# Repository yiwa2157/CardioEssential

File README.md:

# CardioEssential
This repo has the code for controlling the MCU on CardioWear. MCU listens to different commands through UART, and start sampling different signals.
command = "A" : sampling and transmitting ECG signal @ 200Hz
command = "B" : sampling and transmitting temperature signal 
command = "C" : stop sampling, enter idle mode

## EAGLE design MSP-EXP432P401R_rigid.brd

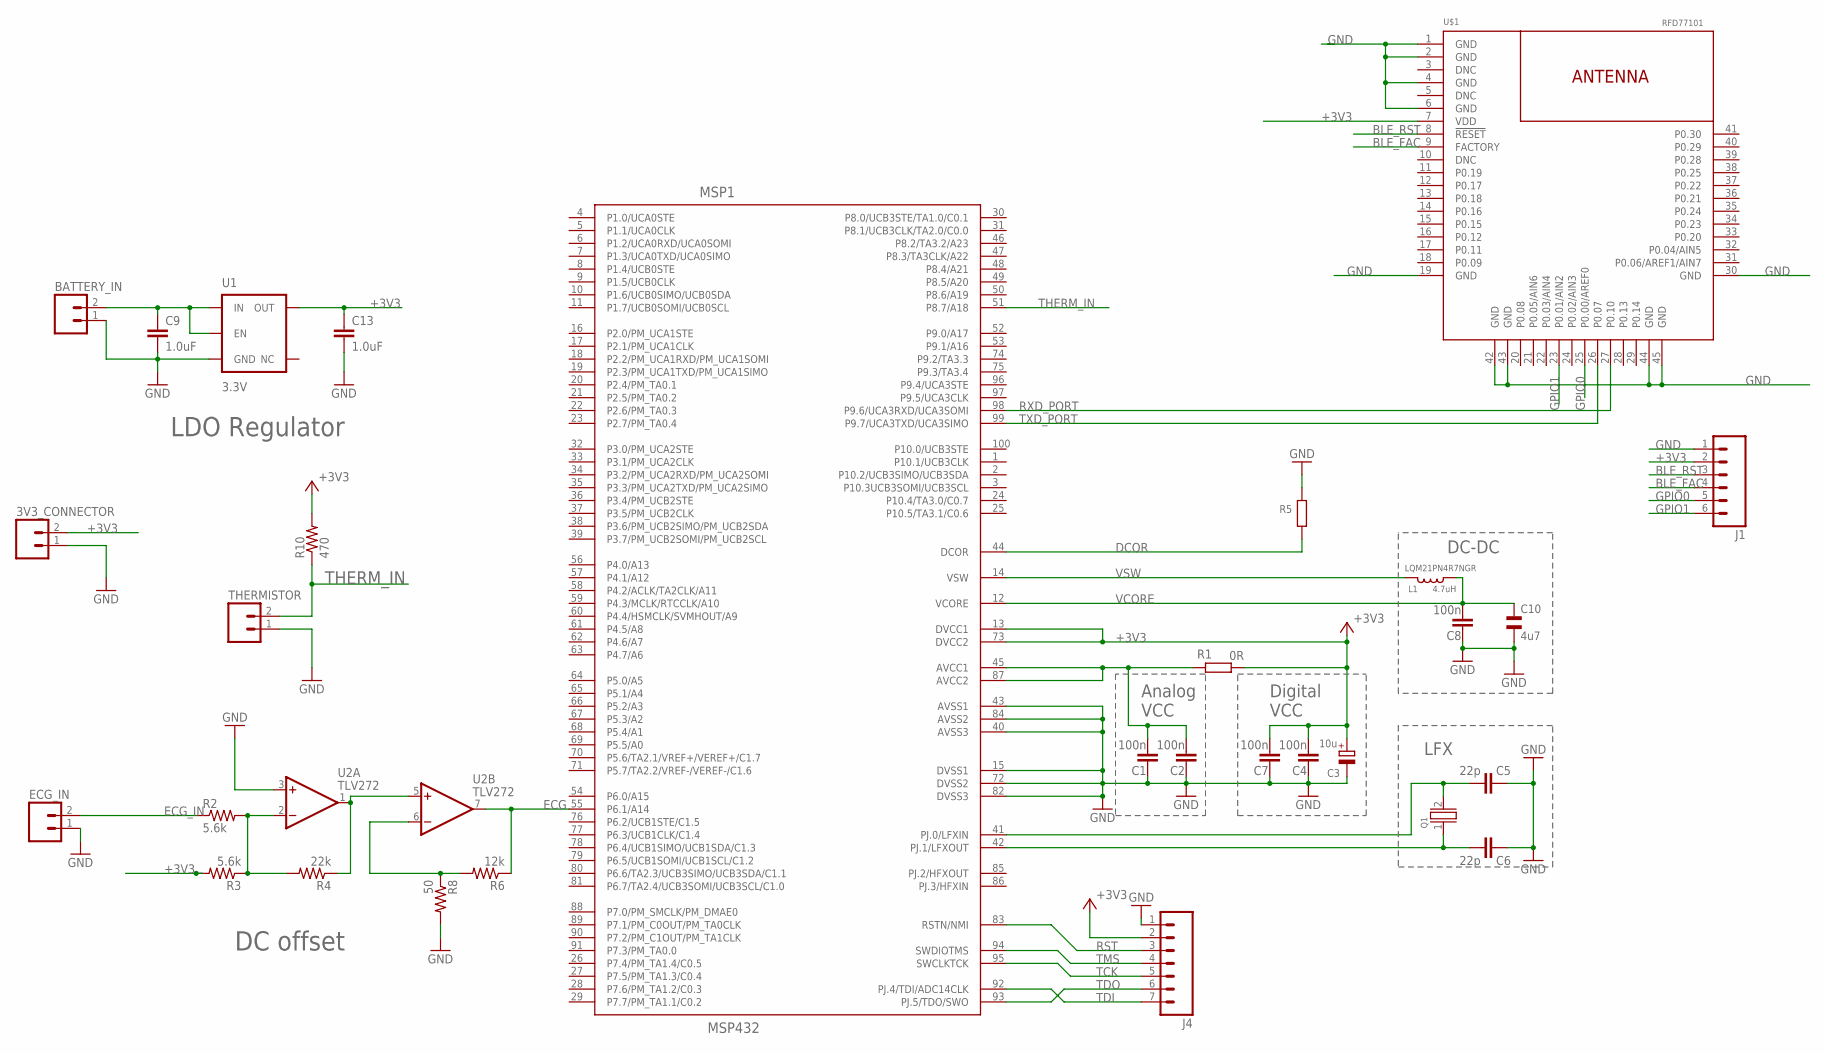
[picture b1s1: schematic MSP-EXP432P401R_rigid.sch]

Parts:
3V3_CONNECTOR: M02PTH; 1X02
BATTERY_IN: M02PTH; 1X02
C1, C2, C4, C7, C8: 100n; 0402
C3: 10u; A/3216-18R
C5, C6: 22p; 0402
C9, C13: 1.0uF; 0805-CAP
C10: 4u7; CSMD0805
ECG_IN: M02PTH; 1X02
J1: M06SILK_FEMALE_PTH; 1X06
J4: M07; 1X07
L1: 4.7uH; 0806
MSP1: MSP432; PZ100
Q1: CRYSTALLF_GENERAL; LF_XTAL
R1: 0R; 0402
R2, R3: 5.6k; 0402-RES
R4: 22k; 0402-RES
R5: R_0805; 0805
R6: 12k; 0402-RES
R8: 50; 0402-RES
R10: 470; 0402-RES
THERMISTOR: M02PTH; 1X02
U1: 3.3V; SOT23-5
U2: TLV272; SO08
U$1: RFD77101

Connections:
+3V3: 3V3_CONNECTOR.2, C3.+, C4.1, C7.1, C13.1, J1.2, J4.2, MSP1.13 (DVCC1), MSP1.73 (DVCC2), R1.1, R3.2, R10.2, U1.5 (OUT), U$1.7 (VDD)
BLE_FAC: J1.4, U$1.9 (FACTORY)
BLE_RST: J1.3, U$1.8 (!RESET!)
DCOR: MSP1.44 (DCOR), R5.1
ECG: MSP1.55 (P6.1/A14), R6.1, U2.7 (OUT)
ECG_IN: ECG_IN.2, R2.1
GND: 3V3_CONNECTOR.1, BATTERY_IN.1, C1.2, C2.2, C3.-, C4.2, C5.2, C6.2, C7.2, C8.2, C9.2, C10.2, C13.2, ECG_IN.1, J1.1, J4.1, MSP1.15 (DVSS1), MSP1.40 (AVSS3), MSP1.43 (AVSS1), MSP1.72 (DVSS2), MSP1.82 (DVSS3), MSP1.84 (AVSS2), R5.2, R8.2, THERMISTOR.1, U1.2 (GND), U2.3 (+IN), U$1.1 (GND), U$1.2 (GND), U$1.4 (GND), U$1.6 (GND), U$1.19 (GND), U$1.30 (GND), U$1.42 (GND), U$1.43 (GND), U$1.44 (GND), U$1.45 (GND)
GPIO0: J1.5, U$1.25 (P0.00/AREF0)
GPIO1: J1.6, U$1.23 (P0.01/AIN2)
unnamed: BATTERY_IN.2, C9.1, U1.1 (IN), U1.3 (EN)
unnamed: R2.2, R3.1, R4.2, U2.2 (-IN)
unnamed: C1.1, C2.1, MSP1.45 (AVCC1), MSP1.87 (AVCC2), R1.2
unnamed: R4.1, U2.1 (OUT), U2.5 (+IN)
unnamed: R6.2, R8.1, U2.6 (-IN)
unnamed: C6.1, MSP1.42 (PJ.1/LFXOUT), Q1.1
unnamed: C5.1, MSP1.41 (PJ.0/LFXIN), Q1.2
P1.0/UCA0STE: MSP1.4 (P1.0/UCA0STE)
P1.1/UCA0CLK: MSP1.5 (P1.1/UCA0CLK)
P1.2/UCA0RXD/UCA0SOMI: MSP1.6 (P1.2/UCA0RXD/UCA0SOMI)
P1.3/UCA0TXD/UCA0SIMO: MSP1.7 (P1.3/UCA0TXD/UCA0SIMO)
P1.4/UCB0STE: MSP1.8 (P1.4/UCB0STE)
P1.5/UCB0CLK: MSP1.9 (P1.5/UCB0CLK)
P1.6/UCB0SIMO/UCB0SDA: MSP1.10 (P1.6/UCB0SIMO/UCB0SDA)
P1.7/UCB0SOMI/UCB0SCL: MSP1.11 (P1.7/UCB0SOMI/UCB0SCL)
P2.0/PM_UCA1STE: MSP1.16 (P2.0/PM_UCA1STE)
P2.1/PM_UCA1CLK: MSP1.17 (P2.1/PM_UCA1CLK)
P2.2/PM_UCA1RXD/PM_UCA1SOMI: MSP1.18 (P2.2/PM_UCA1RXD/PM_UCA1SOMI)
P2.3/PM_UCA1TXD/PM_UCA1SIMO: MSP1.19 (P2.3/PM_UCA1TXD/PM_UCA1SIMO)
P2.4/PM_TA0.1: MSP1.20 (P2.4/PM_TA0.1)
P2.5/PM_TA0.2: MSP1.21 (P2.5/PM_TA0.2)
P2.6/PM_TA0.3: MSP1.22 (P2.6/PM_TA0.3)
P2.7/PM_TA0.4: MSP1.23 (P2.7/PM_TA0.4)
P3.0/PM_UCA2STE: MSP1.32 (P3.0/PM_UCA2STE)
P3.1/PM_UCA2CLK: MSP1.33 (P3.1/PM_UCA2CLK)
P3.2/PM_UCA2RXD/PM_UCA2SOMI: MSP1.34 (P3.2/PM_UCA2RXD/PM_UCA2SOMI)
P3.3/PM_UCA2TXD/PM_UCA2SIMO: MSP1.35 (P3.3/PM_UCA2TXD/PM_UCA2SIMO)
P3.4/PM_UCB2STE: MSP1.36 (P3.4/PM_UCB2STE)
P3.5/PM_UCB2CLK: MSP1.37 (P3.5/PM_UCB2CLK)
P3.6/PM_UCB2SIMO/PM_UCB2SDA: MSP1.38 (P3.6/PM_UCB2SIMO/PM_UCB2SDA)
P3.7/PM_UCB2SOMI/PM_UCB2SCL: MSP1.39 (P3.7/PM_UCB2SOMI/PM_UCB2SCL)
P4.0/A13: MSP1.56 (P4.0/A13)
P4.1/A12: MSP1.57 (P4.1/A12)
P4.2/ACLK/TA2CLK/A11: MSP1.58 (P4.2/ACLK/TA2CLK/A11)
P4.3/MCLK/RTCCLK/A10: MSP1.59 (P4.3/MCLK/RTCCLK/A10)
P4.4/HSMCLK/SVMHOUT/A9: MSP1.60 (P4.4/HSMCLK/SVMHOUT/A9)
P4.5/A8: MSP1.61 (P4.5/A8)
P4.6/A7: MSP1.62 (P4.6/A7)
P4.7/A6: MSP1.63 (P4.7/A6)
P5.0/A5: MSP1.64 (P5.0/A5)
P5.1/A4: MSP1.65 (P5.1/A4)
P5.2/A3: MSP1.66 (P5.2/A3)
P5.3/A2: MSP1.67 (P5.3/A2)
P5.4/A1: MSP1.68 (P5.4/A1)
P5.5/A0: MSP1.69 (P5.5/A0)
P5.6/TA2.1/VREF+/VEREF+/C1.7: MSP1.70 (P5.6/TA2.1/VREF+/VEREF+/C1.7)
P5.7/TA2.2/VREF-/VEREF-/C1.6: MSP1.71 (P5.7/TA2.2/VREF-/VEREF-/C1.6)
P6.0/A15: MSP1.54 (P6.0/A15)
P6.2/UCB1STE/C1.5: MSP1.76 (P6.2/UCB1STE/C1.5)
P6.3/UCB1CLK/C1.4: MSP1.77 (P6.3/UCB1CLK/C1.4)
P6.4/UCB1SIMO/UCB1SDA/C1.3: MSP1.78 (P6.4/UCB1SIMO/UCB1SDA/C1.3)
P6.5/UCB1SOMI/UCB1SCL/C1.2: MSP1.79 (P6.5/UCB1SOMI/UCB1SCL/C1.2)
P6.6/TA2.3/UCB3SIMO/UCB3SDA/C1.1: MSP1.80 (P6.6/TA2.3/UCB3SIMO/UCB3SDA/C1.1)
P6.7/TA2.4/UCB3SOMI/UCB3SCL/C1.0: MSP1.81 (P6.7/TA2.4/UCB3SOMI/UCB3SCL/C1.0)
P7.0/PM_SMCLK/PM_DMAE0: MSP1.88 (P7.0/PM_SMCLK/PM_DMAE0)
P7.1/PM_C0OUT/PM_TA0CLK: MSP1.89 (P7.1/PM_C0OUT/PM_TA0CLK)
P7.2/PM_C1OUT/PM_TA1CLK: MSP1.90 (P7.2/PM_C1OUT/PM_TA1CLK)
P7.3/PM_TA0.0: MSP1.91 (P7.3/PM_TA0.0)
P7.4/PM_TA1.4/C0.5: MSP1.26 (P7.4/PM_TA1.4/C0.5)
P7.5/PM_TA1.3/C0.4: MSP1.27 (P7.5/PM_TA1.3/C0.4)
P7.6/PM_TA1.2/C0.3: MSP1.28 (P7.6/PM_TA1.2/C0.3)
P7.7/PM_TA1.1/C0.2: MSP1.29 (P7.7/PM_TA1.1/C0.2)
P8.0/UCB3STE/TA1.0/C0.1: MSP1.30 (P8.0/UCB3STE/TA1.0/C0.1)
P8.1/UCB3CLK/TA2.0/C0.0: MSP1.31 (P8.1/UCB3CLK/TA2.0/C0.0)
P8.2/TA3.2/A23: MSP1.46 (P8.2/TA3.2/A23)
P8.3/TA3CLK/A22: MSP1.47 (P8.3/TA3CLK/A22)
P8.4/A21: MSP1.48 (P8.4/A21)
P8.5/A20: MSP1.49 (P8.5/A20)
P8.6/A19: MSP1.50 (P8.6/A19)
P9.0/A17: MSP1.52 (P9.0/A17)
P9.1/A16: MSP1.53 (P9.1/A16)
P9.2/TA3.3: MSP1.74 (P9.2/TA3.3)
P9.3/TA3.4: MSP1.75 (P9.3/TA3.4)
P9.4/UCA3STE: MSP1.96 (P9.4/UCA3STE)
P9.5/UCA3CLK: MSP1.97 (P9.5/UCA3CLK)
P10.0/UCB3STE: MSP1.100 (P10.0/UCB3STE)
P10.1/UCB3CLK: MSP1.1 (P10.1/UCB3CLK)
P10.2/UCB3SIMO/UCB3SDA: MSP1.2 (P10.2/UCB3SIMO/UCB3SDA)
P10.3UCB3SOMI/UCB3SCL: MSP1.3 (P10.3UCB3SOMI/UCB3SCL)
P10.4/TA3.0/C0.7: MSP1.24 (P10.4/TA3.0/C0.7)
P10.5/TA3.1/C0.6: MSP1.25 (P10.5/TA3.1/C0.6)
PJ.2/HFXOUT: MSP1.85 (PJ.2/HFXOUT)
PJ.3/HFXIN: MSP1.86 (PJ.3/HFXIN)
RST: J4.3, MSP1.83 (RSTN/NMI)
RXD_PORT: MSP1.98 (P9.6/UCA3RXD/UCA3SOMI), U$1.27 (P0.10)
TCK: J4.5, MSP1.95 (SWCLKTCK)
TDI: J4.7, MSP1.92 (PJ.4/TDI/ADC14CLK)
TDO: J4.6, MSP1.93 (PJ.5/TDO/SWO)
THERM_IN: MSP1.51 (P8.7/A18), R10.1, THERMISTOR.2
TMS: J4.4, MSP1.94 (SWDIOTMS)
TXD_PORT: MSP1.99 (P9.7/UCA3TXD/UCA3SIMO), U$1.26 (P0.07)
V+: U2.8 (V+)
V-: U2.4 (V-)
VCORE: C8.1, C10.1, L1.1, MSP1.12 (VCORE)
VSW: L1.2, MSP1.14 (VSW)

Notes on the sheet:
LQM21PN4R7NGR
LFX
Analog
VCC
Digital
DC-DC
DC offset
LDO Regulator

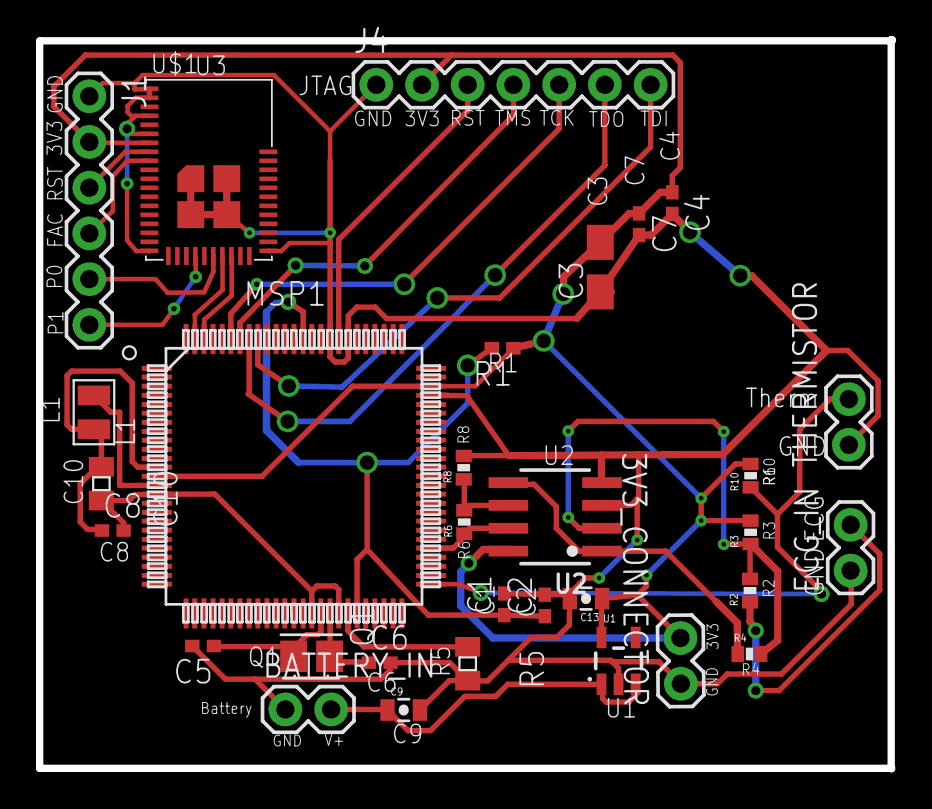
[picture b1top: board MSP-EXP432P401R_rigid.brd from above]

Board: 2 copper layers, 47.4 x 40.5 mm, 31 parts (0 on the bottom side), 26 nets.

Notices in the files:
parts and their libraries:
SparkFun-Connectors: Licensing: Creative Commons ShareAlike 4.0 International - https://creativecommons.org/licenses/by-sa/4.0
RFDigital: © 2015 RF Digital Corporation
op-amp: Copyright (C) 2006 by Bob Starr
